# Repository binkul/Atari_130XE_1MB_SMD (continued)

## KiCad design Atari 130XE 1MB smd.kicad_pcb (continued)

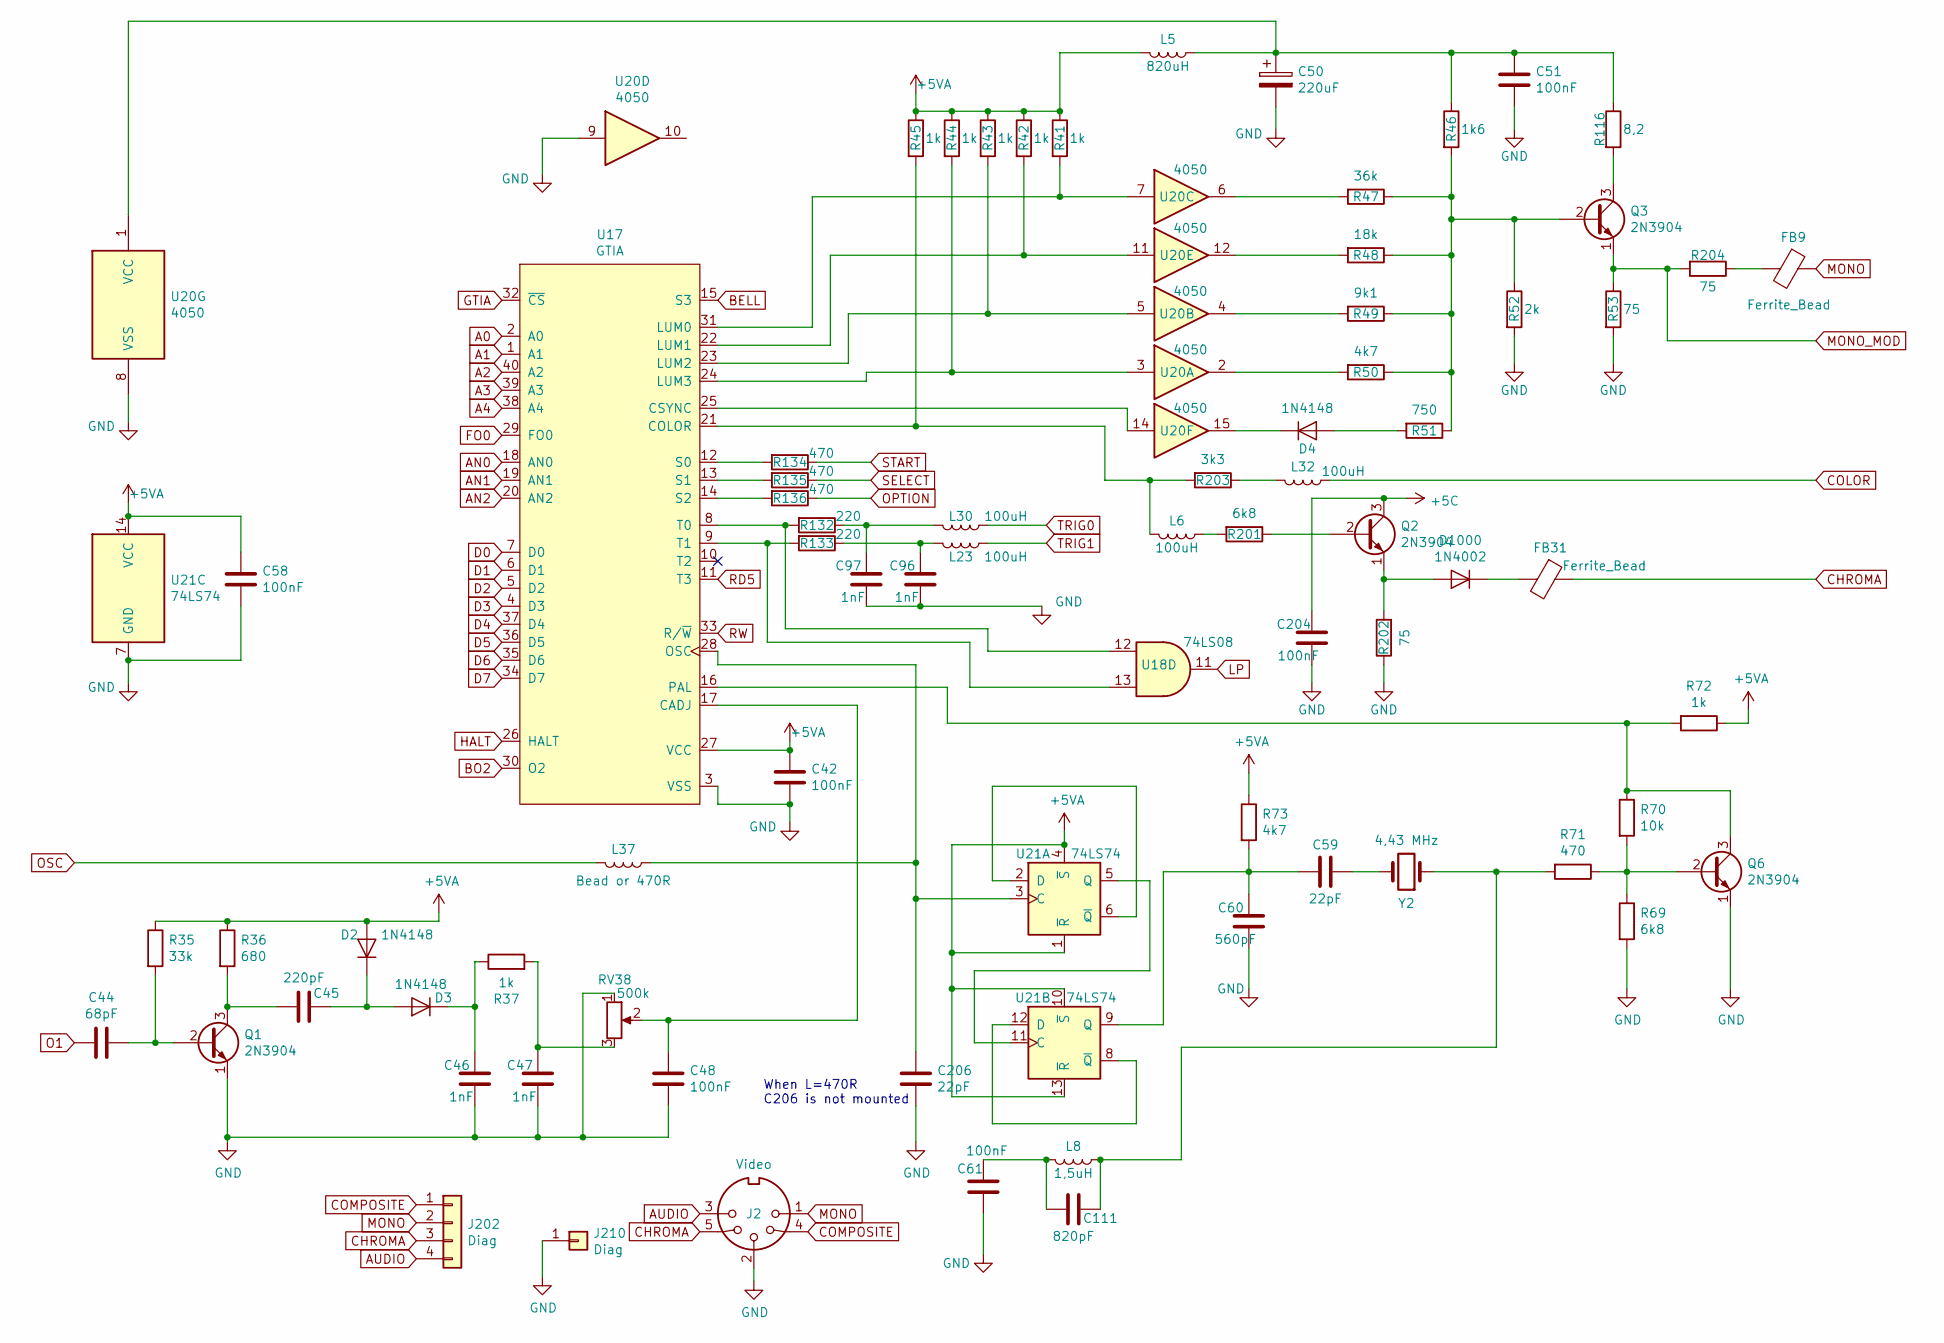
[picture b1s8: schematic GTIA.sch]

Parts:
C42, C48, C51, C58, C61, C204: 100nF; C_1206_3216Metric_Pad1.42x1.75mm_HandSolder
C44: 68pF; C_1206_3216Metric_Pad1.42x1.75mm_HandSolder
C45: 220pF; C_1206_3216Metric_Pad1.42x1.75mm_HandSolder
C46, C47, C96, C97: 1nF; C_1206_3216Metric_Pad1.42x1.75mm_HandSolder
C50: 220uF; CP_Radial_D5.0mm_P2.00mm
C59, C206: 22pF; C_1206_3216Metric_Pad1.42x1.75mm_HandSolder
C60: 560pF; C_1206_3216Metric_Pad1.42x1.75mm_HandSolder
C111: 820pF; C_1206_3216Metric_Pad1.42x1.75mm_HandSolder
D2, D3, D4: 1N4148; D_MiniMELF
D1000: 1N4002; D_MELF_Handsoldering
FB9, FB31: Ferrite_Bead; L_1812_4532Metric_Pad1.30x3.40mm_HandSolder
J2: Video; DIN_5_pin
J202: Diag; PinHeader_1x04_P2.54mm_Vertical
J210: Diag; PinHeader_1x01_P2.54mm_Vertical
L5: 820uH; L_1812_4532Metric_Pad1.30x3.40mm_HandSolder
L6, L23, L30, L32: 100uH; L_1812_4532Metric_Pad1.30x3.40mm_HandSolder
L8: 1,5uH; L_1812_4532Metric_Pad1.30x3.40mm_HandSolder
L37: Bead or 470R; C_1206_3216Metric_Pad1.42x1.75mm_HandSolder
Q1, Q2, Q3: 2N3904; TO-92L_Wide
Q6: 2N3904; TO-92
R35: 33k; R_1206_3216Metric_Pad1.42x1.75mm_HandSolder
R36: 680; R_1206_3216Metric_Pad1.42x1.75mm_HandSolder
R37, R41, R42, R43, R44, R45, R72: 1k; R_1206_3216Metric_Pad1.42x1.75mm_HandSolder
R46: 1k6; R_1206_3216Metric_Pad1.42x1.75mm_HandSolder
R47: 36k; R_1206_3216Metric_Pad1.42x1.75mm_HandSolder
R48: 18k; R_1206_3216Metric_Pad1.42x1.75mm_HandSolder
R49: 9k1; R_1206_3216Metric_Pad1.42x1.75mm_HandSolder
R50, R73: 4k7; R_1206_3216Metric_Pad1.42x1.75mm_HandSolder
R51: 750; R_1206_3216Metric_Pad1.42x1.75mm_HandSolder
R52: 2k; R_1206_3216Metric_Pad1.42x1.75mm_HandSolder
R53, R202, R204: 75; R_1206_3216Metric_Pad1.42x1.75mm_HandSolder
R69, R201: 6k8; R_1206_3216Metric_Pad1.42x1.75mm_HandSolder
R70: 10k; R_1206_3216Metric_Pad1.42x1.75mm_HandSolder
R71, R134, R135, R136: 470; R_1206_3216Metric_Pad1.42x1.75mm_HandSolder
R116: 8,2; R_1206_3216Metric_Pad1.42x1.75mm_HandSolder
R132, R133: 220; R_1206_3216Metric_Pad1.42x1.75mm_HandSolder
R203: 3k3; R_1206_3216Metric_Pad1.42x1.75mm_HandSolder
RV38: 500k; Potentiometer_ACP_CA9-V10_Vertical_Hole
U17: GTIA; DIP-40_W15.24mm_Socket
U18: 74LS08; DIP-14_W7.62mm_Socket
U20: 4050; DIP-16_W7.62mm_Socket
U21: 74LS74; DIP-14_W7.62mm_Socket
Y2: 4,43 MHz; Crystal_HC18-U_Horizontal

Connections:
+5C: C204.2, Q2.3 (C); also elsewhere on the board
+5VA: C42.1, C58.1, D2.2 (A), L5.2, R35.1, R36.1, R41.1, R42.1, R43.1, R44.1, R45.1, R72.1, R73.1, U17.27 (VCC), U21.1 (~R), U21.4 (~S), U21.10 (~S), U21.13 (~R), U21.14 (VCC); also elsewhere on the board
A0: U17.2 (A0); also elsewhere on the board
A1: U17.1 (A1); also elsewhere on the board
A2: U17.40 (A2); also elsewhere on the board
A3: U17.39 (A3); also elsewhere on the board
A4: U17.38 (A4); also elsewhere on the board
AN0: U17.18 (AN0); also elsewhere on the board
AN1: U17.19 (AN1); also elsewhere on the board
AN2: U17.20 (AN2); also elsewhere on the board
AUDIO: J2.3, J202.4; also elsewhere on the board
BELL: U17.15 (S3); also elsewhere on the board
BO2: U17.30 (O2); also elsewhere on the board
CHROMA: FB31.1, J2.5, J202.3
COLOR: L32.1; also elsewhere on the board
COMPOSITE: J2.4, J202.1; also elsewhere on the board
D0: U17.7 (D0); also elsewhere on the board
D1: U17.6 (D1); also elsewhere on the board
D2: U17.5 (D2); also elsewhere on the board
D3: U17.4 (D3); also elsewhere on the board
D4: U17.37 (D4); also elsewhere on the board
D5: U17.36 (D5); also elsewhere on the board
D6: U17.35 (D6); also elsewhere on the board
D7: U17.34 (D7); also elsewhere on the board
FO0: U17.29 (FO0); also elsewhere on the board
GND: C42.2, C46.1, C47.1, C48.1, C50.2, C51.2, C58.2, C60.1, C61.1, C96.1, C97.1, C204.1, C206.1, J2.2, J210.1, Q1.1 (E), Q6.1 (E), R52.2, R53.2, R69.2, R202.1, RV38.1, U17.3 (VSS), U20.8 (VSS), U20.9, U21.7 (GND); also elsewhere on the board
GTIA: U17.32 (~CS); also elsewhere on the board
HALT: U17.26 (HALT); also elsewhere on the board
LP: U18.11; also elsewhere on the board
MONO: FB9.1, J2.1, J202.2
MONO_MOD: Q3.1 (E), R53.1, R204.2; also elsewhere on the board
unnamed: C44.1, Q1.2 (B), R35.2
unnamed: C45.1, D2.1 (K), D3.2 (A)
unnamed: C45.2, Q1.3 (C), R36.2
unnamed: C46.2, D3.1 (K), R37.1
unnamed: C47.2, R37.2, RV38.3
unnamed: C48.2, RV38.2, U17.17 (CADJ)
unnamed: C50.1, C51.1, L5.1, R46.1, R116.1, U20.1 (VCC)
unnamed: C59.1, C60.2, R73.2, U21.9 (Q)
unnamed: C59.2, Y2.2
unnamed: C96.2, L23.2, R133.1
unnamed: C97.2, L30.2, R132.1
unnamed: C111.1, L8.1, R71.2, Y2.1
unnamed: C61.2, C111.2, L8.2
unnamed: C206.2, L37.1, U17.28 (OSC), U21.3 (C)
unnamed: D4.1 (K), U20.15
unnamed: D4.2 (A), R51.2
unnamed: D1000.1 (K), FB31.2
unnamed: D1000.2 (A), Q2.1 (E), R202.2
unnamed: FB9.2, R204.1
unnamed: L6.1, R201.2
unnamed: L6.2, R45.2, R203.2, U17.21 (COLOR)
unnamed: L32.2, R203.1
unnamed: Q2.2 (B), R201.1
unnamed: Q3.2 (B), R46.2, R47.1, R48.1, R49.1, R50.1, R51.1, R52.1
unnamed: Q3.3 (C), R116.2
unnamed: Q6.2 (B), R69.1, R70.2, R71.1
unnamed: Q6.3 (C), R70.1, R72.2, U17.16 (PAL)
unnamed: R41.2, U17.31 (LUM0), U20.7
unnamed: R42.2, U17.22 (LUM1), U20.11
unnamed: R43.2, U17.23 (LUM2), U20.5
unnamed: R44.2, U17.24 (LUM3), U20.3
unnamed: R47.2, U20.6
unnamed: R48.2, U20.12
unnamed: R49.2, U20.4
unnamed: R50.2, U20.2
unnamed: R132.2, U17.8 (T0), U18.12
unnamed: R133.2, U17.9 (T1), U18.13
unnamed: R134.2, U17.12 (S0)
unnamed: R135.2, U17.13 (S1)
unnamed: R136.2, U17.14 (S2)
unnamed: U17.25 (CSYNC), U20.14
unnamed: U21.2 (D), U21.6 (~Q)
unnamed: U21.5 (Q), U21.11 (C)
unnamed: U21.8 (~Q), U21.12 (D)
O1: C44.2; also elsewhere on the board
OPTION: R136.1; also elsewhere on the board
OSC: L37.2; also elsewhere on the board
RD5: U17.11 (T3); also elsewhere on the board
RW: U17.33 (R/~W); also elsewhere on the board
SELECT: R135.1; also elsewhere on the board
START: R134.1; also elsewhere on the board
TRIG0: L30.1; also elsewhere on the board
TRIG1: L23.1; also elsewhere on the board

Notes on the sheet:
When L=470R C206 is not mounted

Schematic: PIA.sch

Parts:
C68: 100nF; C_1206_3216Metric_Pad1.42x1.75mm_HandSolder
C79: 22uF; CP_Radial_D7.5mm_P2.50mm
C80: 1nF; R_1206_3216Metric_Pad1.42x1.75mm_HandSolder
C81, C82, C83, C84, C85, C86, C87, C88, C89, C90, C91, C92: 1nF; C_1206_3216Metric_Pad1.42x1.75mm_HandSolder
FB10, FB11: Ferrite_Bead; L_1812_4532Metric_Pad1.30x3.40mm_HandSolder
L19, L20, L21, L22, L26, L27, L28, L29: 10uH; L_1812_4532Metric_Pad1.30x3.40mm_HandSolder
Q4: 2N3906; TO-92_Wide
R23, R24, R25, R85, R86, R87, R88, R501: 3k; R_1206_3216Metric_Pad1.42x1.75mm_HandSolder
R91: 2k7; R_1206_3216Metric_Pad1.42x1.75mm_HandSolder
R92, R93, R94: 4k7; R_1206_3216Metric_Pad1.42x1.75mm_HandSolder
R117, R119: 100; R_1206_3216Metric_Pad1.42x1.75mm_HandSolder
R118, R120, R121, R122, R123, R124, R125, R126, R127: 220; R_1206_3216Metric_Pad1.42x1.75mm_HandSolder
R206: 3k3; R_1206_3216Metric_Pad1.42x1.75mm_HandSolder
U23: PIA; DIP-40_W15.24mm_Socket

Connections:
+5VA: C68.1, FB10.2, Q4.1 (E), R23.1, R24.1, R25.1, R85.1, R86.1, R87.1, R88.1, R92.1, R93.2, R94.2, R206.1, R501.1, U23.20 (VCC); also elsewhere on the board
A0: U23.35 (A0); also elsewhere on the board
A1: U23.36 (A1); also elsewhere on the board
BACK0: L28.1; also elsewhere on the board
BACK1: L21.1; also elsewhere on the board
BO2: U23.25 (O2); also elsewhere on the board
COMMAND: C84.1, R119.1; also elsewhere on the board
D0: U23.33 (D0); also elsewhere on the board
D1: U23.32 (D1); also elsewhere on the board
D2: U23.31 (D2); also elsewhere on the board
D3: U23.30 (D3); also elsewhere on the board
D4: U23.29 (D4); also elsewhere on the board
D5: U23.28 (D5); also elsewhere on the board
D6: U23.27 (D6); also elsewhere on the board
D7: U23.26 (D7); also elsewhere on the board
FWD0: L29.1; also elsewhere on the board
FWD1: L22.1; also elsewhere on the board
GND: C68.2, C79.2, C80.2, C81.2, C82.2, C83.2, C84.2, C85.2, C86.2, C87.2, C88.2, C89.2, C90.2, C91.2, C92.2, U23.1 (VSS); also elsewhere on the board
INTRUPT: C83.1, R93.1, R118.1; also elsewhere on the board
IRQ: U23.37 (~IRQB), U23.38 (~IRQA); also elsewhere on the board
LEFT0: L27.1; also elsewhere on the board
LEFT1: L20.1; also elsewhere on the board
MTR_CLR: C81.1, FB11.1; also elsewhere on the board
unnamed: C85.1, L29.2, R120.1
unnamed: C86.1, L28.2, R121.1
unnamed: C87.1, L27.2, R122.1
unnamed: C88.1, L26.2, R123.1
unnamed: C89.1, L22.2, R124.1
unnamed: C90.1, L21.2, R125.1
unnamed: C91.1, L20.2, R126.1
unnamed: C92.1, L19.2, R127.1
unnamed: FB11.2, Q4.3 (C)
unnamed: Q4.2 (B), R91.1
unnamed: R86.2, U23.22 (CS0), U23.24 (CS1)
unnamed: R91.2, U23.39 (CA2)
unnamed: R92.2, R117.2, U23.40 (CA1)
unnamed: R118.2, U23.18 (CB1)
unnamed: R94.1, R119.2, U23.19 (CB2)
unnamed: R120.2, U23.2 (PA0)
unnamed: R121.2, U23.3 (PA1)
unnamed: R122.2, U23.4 (PA2)
unnamed: R123.2, U23.5 (PA3)
unnamed: R124.2, U23.6 (PA4)
unnamed: R125.2, U23.7 (PA5)
unnamed: R126.2, U23.8 (PA6)
unnamed: R127.2, U23.9 (PA7)
PB0: R88.2, U23.10 (PB0); also elsewhere on the board
PB1: R85.2, U23.11 (PB1); also elsewhere on the board
PB2: R23.2, U23.12 (PB2); also elsewhere on the board
PB3: R25.2, U23.13 (PB3); also elsewhere on the board
PB4: R24.2, U23.14 (PB4); also elsewhere on the board
PB5: R206.2, U23.15 (PB5); also elsewhere on the board
PB6: R501.2, U23.16 (PB6); also elsewhere on the board
PB7: R87.2, U23.17 (PB7); also elsewhere on the board
PIA: U23.23 (~CS2); also elsewhere on the board
PROCEED: C82.1, R117.1; also elsewhere on the board
READY: C79.1, C80.1, FB10.1; also elsewhere on the board
RIGHT0: L26.1; also elsewhere on the board
RIGHT1: L19.1; also elsewhere on the board
RST: U23.34 (~RST); also elsewhere on the board
RW: U23.21 (R/~W); also elsewhere on the board

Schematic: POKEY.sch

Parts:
C62, C71, C72, C73, C74, C75, C76, C77, C78: 1nF; C_1206_3216Metric_Pad1.42x1.75mm_HandSolder
C63, C64, C65, C66: 47nF; C_1206_3216Metric_Pad1.42x1.75mm_HandSolder
C69, C70: 100nF; C_1206_3216Metric_Pad1.42x1.75mm_HandSolder
C98: 10uF; CP_Radial_D5.0mm_P2.00mm
D5: 1N4148; D_1206_3216Metric_Pad1.42x1.75mm_HandSolder
J201: Diagnostic; PinHeader_1x04_P2.54mm_Vertical
L15, L16, L17, L18: 10uH; L_1812_4532Metric_Pad1.30x3.40mm_HandSolder
R74: 3k; R_1206_3216Metric_Pad1.42x1.75mm_HandSolder
R76, R77, R78, R79: 1k8; R_1206_3216Metric_Pad1.42x1.75mm_HandSolder
R80: 1k; R_1206_3216Metric_Pad1.42x1.75mm_HandSolder
R81, R82, R83, R84: 4k7; R_1206_3216Metric_Pad1.42x1.75mm_HandSolder
R89, R96: 47k; R_1206_3216Metric_Pad1.42x1.75mm_HandSolder
R90, R128, R129, R130, R131: 100; R_1206_3216Metric_Pad1.42x1.75mm_HandSolder
R137: 270; R_1206_3216Metric_Pad1.42x1.75mm_HandSolder
R138, R139, R140, R141, R142, R143, R144, R145, R146, R147, R148, R149, R150, R151, R152, R153: 220; R_1206_3216Metric_Pad1.42x1.75mm_HandSolder
U22: POKEY; DIP-40_W15.24mm_Socket
U24, U25: CD4051B; DIP-16_W7.62mm_Socket

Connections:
+5P: C62.1, C98.1, U22.17 (VCC); also elsewhere on the board
+5VA: C69.1, C70.1, D5.1 (K), R74.1, R80.2, R81.1, R82.1, R83.1, R84.1, R89.2, R96.2, U24.16 (VDD), U25.16 (VDD); also elsewhere on the board
A0: U22.36 (A0); also elsewhere on the board
A1: U22.35 (A1); also elsewhere on the board
A2: U22.34 (A2); also elsewhere on the board
A3: U22.33 (A3); also elsewhere on the board
BO2: U22.7 (O2); also elsewhere on the board
BSC: R137.1; also elsewhere on the board
CLK_IN: C76.1, J201.1, R129.1; also elsewhere on the board
CLK_OUT: C75.1, J201.2, R128.1; also elsewhere on the board
D0: U22.38 (D0); also elsewhere on the board
D1: U22.39 (D1); also elsewhere on the board
D2: U22.40 (D2); also elsewhere on the board
D3: U22.2 (D3); also elsewhere on the board
D4: U22.3 (D4); also elsewhere on the board
D5: U22.4 (D5); also elsewhere on the board
D6: U22.5 (D6); also elsewhere on the board
D7: U22.6 (D7); also elsewhere on the board
DATA_IN: C77.1, J201.3, R130.1; also elsewhere on the board
DATA_OUT: C78.1, J201.4, R131.1; also elsewhere on the board
GND: C62.2, C63.2, C64.2, C65.2, C66.2, C69.2, C70.2, C71.2, C72.2, C73.2, C74.2, C75.2, C76.2, C77.2, C78.2, C98.2, R90.2, U22.1 (VSS), U22.8 (P6), U22.9 (P7), U22.10 (P4), U22.11 (P5), U24.6 (INH), U24.7 (VEE), U24.8 (VSS), U25.6 (INH), U25.7 (VEE), U25.8 (VSS); also elsewhere on the board
IN0: R146.1; also elsewhere on the board
IN1: R147.1; also elsewhere on the board
IN2: R148.1; also elsewhere on the board
IN3: R149.1; also elsewhere on the board
IN4: R150.1; also elsewhere on the board
IN5: R151.1; also elsewhere on the board
IN6: R152.1; also elsewhere on the board
IN7: R153.1; also elsewhere on the board
IRQ: U22.29 (~IRQ); also elsewhere on the board
K0: U22.23 (~K0), U24.11 (A)
K1: U22.22 (~K1), U24.10 (B)
K2: U22.21 (~K2), U24.9 (C)
K3: U22.20 (~K3), U25.11 (A)
K4: U22.19 (~K4), U25.10 (B)
K5: U22.18 (~K5), U25.9 (C)
unnamed: C63.1, R78.2, U22.13 (P3)
unnamed: C64.1, R76.2, U22.15 (P1)
unnamed: C65.1, R77.2, U22.14 (P0)
unnamed: C66.1, R79.2, U22.12 (P2)
unnamed: C71.1, L17.2, R76.1
unnamed: C72.1, L18.2, R77.1
unnamed: C73.1, L15.2, R78.1
unnamed: C74.1, L16.2, R79.1
unnamed: D5.2 (A), R96.1, R137.2, U22.16 (~KR2)
unnamed: R74.2, U22.31 (CS1)
unnamed: R89.1, U22.25 (~KR1), U24.3 (X)
unnamed: R90.1, U25.3 (X)
unnamed: R81.2, R128.2, U22.27 (ACLK)
unnamed: R82.2, R129.2, U22.26 (BCLK)
unnamed: R83.2, R130.2, U22.24 (SID)
unnamed: R84.2, R131.2, U22.28 (SOD)
unnamed: R138.2, U25.4 (X7)
unnamed: R139.2, U25.2 (X6)
unnamed: R140.2, U25.5 (X5)
unnamed: R141.2, U25.1 (X4)
unnamed: R142.2, U25.12 (X3)
unnamed: R143.2, U25.15 (X2)
unnamed: R144.2, U25.14 (X1)
unnamed: R145.2, U25.13 (X0)
unnamed: R146.2, U24.13 (X0)
unnamed: R147.2, U24.14 (X1)
unnamed: R148.2, U24.15 (X2)
unnamed: R149.2, U24.12 (X3)
unnamed: R150.2, U24.1 (X4)
unnamed: R151.2, U24.5 (X5)
unnamed: R152.2, U24.2 (X6)
unnamed: R153.2, U24.4 (X7)
OUT0: R145.1; also elsewhere on the board
OUT1: R144.1; also elsewhere on the board
OUT2: R143.1; also elsewhere on the board
OUT3: R142.1; also elsewhere on the board
OUT4: R141.1; also elsewhere on the board
OUT5: R140.1; also elsewhere on the board
OUT6: R139.1; also elsewhere on the board
OUT7: R138.1; also elsewhere on the board
POKEY: U22.30 (~CS0); also elsewhere on the board
POT_A0: L18.1; also elsewhere on the board
POT_A1: L16.1; also elsewhere on the board
POT_B0: L17.1; also elsewhere on the board
POT_B1: L15.1; also elsewhere on the board
RW: U22.32 (R/~W); also elsewhere on the board
SOUND: R80.1, U22.37 (AUDIO); also elsewhere on the board

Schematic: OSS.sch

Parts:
C28, C99: 100nF; C_1206_3216Metric_Pad1.42x1.75mm_HandSolder
C203: 1uF; C_1206_3216Metric_Pad1.42x1.75mm_HandSolder
D100, D101: 1N4148; D_1206_3216Metric_Pad1.42x1.75mm_HandSolder
J501: TPP_sel; PinHeader_2x02_P2.54mm_Vertical
R508, R509: 4k7; R_1206_3216Metric_Pad1.42x1.75mm_HandSolder
R510: 10k; R_1206_3216Metric_Pad1.42x1.75mm_HandSolder
U5: 27C010; PLCC-32_THT-Socket
U104: 74LS157; SOIC-16_3.9x9.9mm_P1.27mm
U105: 74HC74; SOIC-14_3.9x8.7mm_P1.27mm

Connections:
+5VA: C28.1, C99.1, D100.1 (K), R508.1, R509.2, R510.2, U5.1 (VPP), U5.31 (~PGM), U5.32 (VCC), U104.16 (VCC), U105.10 (~S), U105.13 (~R), U105.14 (VCC); also elsewhere on the board
A0: U5.12 (A0); also elsewhere on the board
A1: U5.11 (A1); also elsewhere on the board
A2: U5.10 (A2); also elsewhere on the board
A3: U5.9 (A3); also elsewhere on the board
A4: U5.8 (A4); also elsewhere on the board
A5: U5.7 (A5); also elsewhere on the board
A6: U5.6 (A6); also elsewhere on the board
A7: U5.5 (A7); also elsewhere on the board
A8: U5.27 (A8); also elsewhere on the board
A9: U5.26 (A9); also elsewhere on the board
A10: U5.23 (A10); also elsewhere on the board
A11: U5.25 (A11); also elsewhere on the board
A12: U5.4 (A12); also elsewhere on the board
A13: U5.28 (A13); also elsewhere on the board
A16: U104.11 (I0c), U105.5 (Q)
D0: U5.13 (D0); also elsewhere on the board
D1: U5.14 (D1); also elsewhere on the board
D2: U5.15 (D2); also elsewhere on the board
D3: U5.17 (D3); also elsewhere on the board
D4: U5.18 (D4); also elsewhere on the board
D5: U5.19 (D5); also elsewhere on the board
D6: U5.20 (D6); also elsewhere on the board
D6XX: U105.3 (C); also elsewhere on the board
D7: U5.21 (D7); also elsewhere on the board
GND: C28.2, C99.2, C203.2, J501.2, J501.4, U5.16 (GND), U104.3 (I1a), U104.6 (I1b), U104.8 (GND), U104.10 (I1c), U104.13 (I1d), U104.14 (I0d), U104.15 (E), U105.2 (D), U105.7 (GND), U105.11 (C), U105.12 (D); also elsewhere on the board
unnamed: C203.1, D100.2 (A), R508.2, U105.1 (~R)
unnamed: D101.1 (K), J501.3, R509.1, U105.4 (~S)
unnamed: J501.1, R510.1, U104.1 (S)
unnamed: U5.3 (A15), U104.4 (Za)
unnamed: U5.29 (A14), U104.7 (Zb)
unnamed: U5.2 (A16), U104.9 (Zc)
OS: U5.22 (~CE), U5.24 (~OE); also elsewhere on the board
PB2: U104.5 (I0b); also elsewhere on the board
PB3: U104.2 (I0a); also elsewhere on the board
RST: D101.2 (A); also elsewhere on the board

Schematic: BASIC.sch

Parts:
C27, C207, C208, C209, C210: 100nF; C_1206_3216Metric_Pad1.42x1.75mm_HandSolder
C211: 22uF; CP_EIA-3528-21_Kemet-B_Pad1.50x2.35mm_HandSolder
C212: 4u7; CP_EIA-3528-21_Kemet-B_Pad1.50x2.35mm_HandSolder
J500: Basic_sel; PinHeader_2x04_P2.54mm_Vertical
R502: 1k; R_1206_3216Metric_Pad1.42x1.75mm_HandSolder
R503, R504, R505, R506: 10k; R_1206_3216Metric_Pad1.42x1.75mm_HandSolder
R507: 1k2; R_1206_3216Metric_Pad1.42x1.75mm_HandSolder
U4: 27C010; PLCC-32_THT-Socket
U100: 74LS157; SOIC-16_3.9x9.9mm_P1.27mm
U101: 74LS74; SOIC-14_3.9x8.7mm_P1.27mm
U102, U103: 74HC02; SOIC-14_3.9x8.7mm_P1.27mm

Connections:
+5VA: C27.1, C207.1, C208.1, C209.1, C210.1, R503.1, R504.1, R505.1, R506.1, R507.1, U4.1 (VPP), U4.31 (~PGM), U4.32 (VCC), U100.16 (VCC), U101.14 (VCC), U102.14 (VCC), U103.14 (VCC); also elsewhere on the board
A0: U4.12 (A0), U101.2 (D); also elsewhere on the board
A1: U4.11 (A1); also elsewhere on the board
A2: U4.10 (A2); also elsewhere on the board
A3: U4.9 (A3), U101.12 (D); also elsewhere on the board
A4: U4.8 (A4); also elsewhere on the board
A5: U4.7 (A5); also elsewhere on the board
A6: U4.6 (A6); also elsewhere on the board
A7: U4.5 (A7); also elsewhere on the board
A8: U4.27 (A8); also elsewhere on the board
A9: U4.26 (A9); also elsewhere on the board
A10: U4.23 (A10); also elsewhere on the board
A11: U4.25 (A11); also elsewhere on the board
A12: U100.3 (I1a), U102.3, U102.5; also elsewhere on the board
A14_sel: J500.3, R505.2, U4.29 (A14)
A15_sel: J500.5, R504.2, U4.3 (A15)
A16_sel: J500.7, R503.2, U4.2 (A16)
BASIC: U100.10 (I1c); also elsewhere on the board
BO2: U102.8, U102.9; also elsewhere on the board
CCTL: U102.11; also elsewhere on the board
D0: U4.13 (D0); also elsewhere on the board
D1: U4.14 (D1); also elsewhere on the board
D2: U4.15 (D2); also elsewhere on the board
D3: U4.17 (D3); also elsewhere on the board
D4: U4.18 (D4); also elsewhere on the board
D5: U4.19 (D5); also elsewhere on the board
D6: U4.20 (D6); also elsewhere on the board
D7: U4.21 (D7); also elsewhere on the board
GND: C27.2, C207.2, C208.2, C209.2, C210.2, C211.2, C212.2, J500.2, J500.4, J500.6, J500.8, R502.2, U4.16 (GND), U100.6 (I1b), U100.8 (GND), U100.15 (E), U101.7 (GND), U102.7 (GND), U103.7 (GND); also elsewhere on the board
unnamed: C211.1, C212.1, R507.2, U101.1 (~R), U101.13 (~R)
unnamed: J500.1, R506.2, U100.1 (S)
unnamed: R502.1, U100.13 (I1d)
unnamed: U100.2 (I0a), U102.1
unnamed: U4.4 (A12), U100.4 (Za)
unnamed: U100.5 (I0b), U102.4
unnamed: U4.28 (A13), U100.7 (Zb)
unnamed: U4.22 (~CE), U4.24 (~OE), U100.9 (Zc)
unnamed: U100.11 (I0c), U103.10
unnamed: U100.14 (I0d), U103.1
unnamed: U101.5 (Q), U103.5
unnamed: U101.6 (~Q), U102.6
unnamed: U101.8 (~Q), U103.6
unnamed: U101.9 (Q), U102.2
unnamed: U101.4 (~S), U101.10 (~S)
unnamed: U101.3 (C), U101.11 (C), U102.13
unnamed: U102.10, U102.12
unnamed: U103.2, U103.3, U103.4, U103.12
unnamed: U103.8, U103.9, U103.13
RD5: U100.12 (Zd); also elsewhere on the board
S5: U103.11; also elsewhere on the board

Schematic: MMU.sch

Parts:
C26: 100nF; C_1206_3216Metric_Pad1.42x1.75mm_HandSolder
R12: 3k; R_Axial_DIN0207_L3.6mm_D2.2mm_P10.16mm_Horizontal
R13, R14: 1k; R_1206_3216Metric_Pad1.42x1.75mm_HandSolder
R15: 3k; R_1206_3216Metric_Pad1.42x1.75mm_HandSolder
U2: 74LS138; DIP-16_W7.62mm_Socket
U3: MMU; DIP-20_W7.62mm_Socket
U18: 74LS08; DIP-14_W7.62mm_Socket

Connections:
+5VA: C26.1, R12.1, R15.1, U2.16 (VCC), U3.20 (VCC); also elsewhere on the board
A8: U2.1 (A0); also elsewhere on the board
A9: U2.2 (A1); also elsewhere on the board
A10: U2.3 (A2); also elsewhere on the board
A11: U3.1 (A11); also elsewhere on the board
A12: U3.2 (A12); also elsewhere on the board
A13: U3.3 (A13); also elsewhere on the board
A14: U3.4 (A14); also elsewhere on the board
A15: U3.5 (A15); also elsewhere on the board
BASIC: U3.13 (~BASIC); also elsewhere on the board
BE: U3.18 (~BE); also elsewhere on the board
CASINH: U3.16 (~CI); also elsewhere on the board
CCTL: U2.10 (O5); also elsewhere on the board
D1XX: U2.14 (O1); also elsewhere on the board
D6XX: U2.9 (O6); also elsewhere on the board
E3: R12.2, U2.6 (E3)
GND: C26.2, R13.2, R14.2, U2.5 (E2), U2.8 (GND), U3.10 (VSS); also elsewhere on the board
GTIA: U18.8; also elsewhere on the board
MAP: U3.6 (~MAP); also elsewhere on the board
MPD: R15.2, U3.14 (~MPD); also elsewhere on the board
unnamed: U2.4 (E1), U3.17 (~IO)
unnamed: U2.15 (O0), U18.9, U18.10
OS: U3.15 (~OS); also elsewhere on the board
PB0: U3.9 (REN); also elsewhere on the board
PIA: U2.12 (O3); also elsewhere on the board
POKEY: U2.13 (O2); also elsewhere on the board
RD4: R14.1, U3.7 (RD4); also elsewhere on the board
RD5: R13.1, U3.8 (RD5); also elsewhere on the board
REF: U3.11 (~REF); also elsewhere on the board
S4: U3.19 (~S4); also elsewhere on the board
S5: U3.12 (~S5); also elsewhere on the board

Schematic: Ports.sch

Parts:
C93: 100nF; C_1206_3216Metric_Pad1.42x1.75mm_HandSolder
C94, C95: 10nF; C_1206_3216Metric_Pad1.42x1.75mm_HandSolder
C102: 1nF; C_1206_3216Metric_Pad1.42x1.75mm_HandSolder
FB12, FB102: Ferrite_Bead; L_1812_4532Metric_Pad1.30x3.40mm_HandSolder
J1: SIO; SIO_Slot
J5, J6: Joystick_Port; Joystick_Pport
J8: Keyboard; PinHeader_1x24_P2.54mm_Vertical
L25: 10uH; L_1812_4532Metric_Pad1.30x3.40mm_HandSolder
R95: 1k; R_1206_3216Metric_Pad1.42x1.75mm_HandSolder

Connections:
+5P: FB12.1, L25.2; also elsewhere on the board
+5VA: C93.1, C94.1, FB12.2, J8.1, R95.2; also elsewhere on the board
BACK0: J6.2 (Back); also elsewhere on the board
BACK1: J5.2 (Back); also elsewhere on the board
BSC: J8.20; also elsewhere on the board
CLK_IN: J1.1 (CLK_IN); also elsewhere on the board
CLK_OUT: J1.2 (CLK_OUT); also elsewhere on the board
COMMAND: J1.7 (Command); also elsewhere on the board
DATA_IN: J1.3 (Data_In); also elsewhere on the board
DATA_OUT: J1.5 (Data_Out); also elsewhere on the board
FWD0: J6.1 (FWD); also elsewhere on the board
FWD1: J5.1 (FWD); also elsewhere on the board
GND: C93.2, C94.2, C95.2, C102.2, J1.4 (GND), J1.6 (GND), J5.8 (GND), J6.8 (GND), J8.3; also elsewhere on the board
IN0: J8.17; also elsewhere on the board
IN1: J8.11; also elsewhere on the board
IN2: J8.8; also elsewhere on the board
IN3: J8.16; also elsewhere on the board
IN4: J8.19; also elsewhere on the board
IN5: J8.10; also elsewhere on the board
IN6: J8.4; also elsewhere on the board
IN7: J8.9; also elsewhere on the board
INTRUPT: J1.13 (Intrupt); also elsewhere on the board
LEFT0: J6.3 (Left); also elsewhere on the board
LEFT1: J5.3 (Left); also elsewhere on the board
MTR_CLR: J1.8 (Mtr_Ctrl); also elsewhere on the board
unnamed: C95.1, J8.2, R95.1
unnamed: C102.1, FB102.1, J5.7 (VCC), J6.7 (VCC)
unnamed: FB102.2, L25.1
OPTION: J8.23; also elsewhere on the board
OUT0: J8.18; also elsewhere on the board
OUT1: J8.13; also elsewhere on the board
OUT2: J8.15; also elsewhere on the board
OUT3: J8.5; also elsewhere on the board
OUT4: J8.14; also elsewhere on the board
OUT5: J8.6; also elsewhere on the board
OUT6: J8.12; also elsewhere on the board
OUT7: J8.7; also elsewhere on the board
POT_A0: J6.9 (Pot_A); also elsewhere on the board
POT_A1: J5.9 (Pot_A); also elsewhere on the board
POT_B0: J6.5 (Pot_B); also elsewhere on the board
POT_B1: J5.5 (Pot_B); also elsewhere on the board
PROCEED: J1.9 (Proceed); also elsewhere on the board
READY: J1.10 (VCC); also elsewhere on the board
RESET: J8.24; also elsewhere on the board
RIGHT0: J6.4 (Right); also elsewhere on the board
RIGHT1: J5.4 (Right); also elsewhere on the board
SELECT: J8.22; also elsewhere on the board
SIOAUDIO: J1.11 (SIO_Audio); also elsewhere on the board
START: J8.21; also elsewhere on the board
TRIG0: J6.6 (Trig); also elsewhere on the board
TRIG1: J5.6 (Trig); also elsewhere on the board

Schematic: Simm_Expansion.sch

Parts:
C120, C121, C122, C124, C125: 100nF; C_1206_3216Metric_Pad1.42x1.75mm_HandSolder
C123: 100uF; CP_Elec_6.3x9.9
J10: Mem_on_off; PinHeader_2x02_P2.54mm_Vertical
J12: Conn_02x04_Odd_Even; PinHeader_2x04_P2.00mm_Vertical
R97, R98: 10k; R_1206_3216Metric_Pad1.42x1.75mm_HandSolder
R110, R111: 33; R_1206_3216Metric_Pad1.42x1.75mm_HandSolder
U40: GAL20V8_DIP; DIP-24_W7.62mm_Socket
U41: 74LS157; SOP-16_4.4x10.4mm_P1.27mm
U42: 74LS175; SOP-16_4.4x10.4mm_P1.27mm
U43, U44: DRAM_1MB_4bit; SOJ-26
U45: 74HC04; SOIC-14_3.9x8.7mm_P1.27mm

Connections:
+5VA: C120.1, C121.1, C122.1, C123.1, C124.1, C125.1, R97.1, R98.1, U40.24 (VCC), U41.16 (VCC), U42.1 (~Mr), U42.16 (VCC), U43.10 (VCC), U44.10 (VCC), U45.14 (VCC); also elsewhere on the board
A14: U40.3 (I2); also elsewhere on the board
A15: U40.4 (I3); also elsewhere on the board
BE: U42.7 (Q1); also elsewhere on the board
CAS: U40.8 (I7); also elsewhere on the board
CASMAN: R110.2; also elsewhere on the board
DQ0: U44.1 (DQ0); also elsewhere on the board
DQ1: U44.2 (DQ1); also elsewhere on the board
DQ2: U44.18 (DQ2); also elsewhere on the board
DQ3: U44.19 (DQ3); also elsewhere on the board
DQ4: U43.1 (DQ0); also elsewhere on the board
DQ5: U43.2 (DQ1); also elsewhere on the board
DQ6: U43.18 (DQ2); also elsewhere on the board
DQ7: U43.19 (DQ3); also elsewhere on the board
FA14: U40.18 (F3); also elsewhere on the board
FA15: U40.19 (F4); also elsewhere on the board
GND: C120.2, C121.2, C122.2, C123.2, C124.2, C125.2, J10.1, J10.3, U40.12 (GND), U40.13 (I11/OE), U41.8 (GND), U41.15 (E), U42.8 (GND), U43.16 (~OE), U43.20 (VSS), U44.16 (~OE), U44.20 (VSS), U45.7 (GND); also elsewhere on the board
HALT: U40.14 (I12); also elsewhere on the board
MAP: U42.2 (Q0); also elsewhere on the board
unnamed: J10.2, R97.2, U40.10 (I9)
unnamed: J10.4, R98.2, U40.9 (I8)
unnamed: J12.4, U45.8
unnamed: J12.6, U45.11, U45.12
unnamed: J12.8, U45.4, U45.5
unnamed: R110.1, U40.17 (F2)
unnamed: R111.1, U43.17 (~CAS), U44.17 (~CAS)
unnamed: R111.2, U40.16 (F1)
unnamed: U40.15 (F0), U42.9 (Cp)
unnamed: U40.22 (F7), U41.2 (I0a)
unnamed: U41.4 (Za), U43.15 (A8), U44.15 (A8)
unnamed: U41.7 (Zb), U43.5 (A9), U44.5 (A9)
unnamed: U45.2, U45.3
unnamed: U45.9, U45.10
unnamed: U45.6, U45.13
O2: U40.21 (F6); also elsewhere on the board
PB1: U41.6 (I1b), U42.5 (D1); also elsewhere on the board
PB2: U40.5 (I4); also elsewhere on the board
PB3: U40.6 (I5); also elsewhere on the board
PB4: U40.7 (I6); also elsewhere on the board
PB5: U40.23 (I13); also elsewhere on the board
PB6: U41.3 (I1a); also elsewhere on the board
PB7: U41.5 (I0b), U42.4 (D0); also elsewhere on the board
RA0: U43.6 (A0), U44.6 (A0); also elsewhere on the board
RA1: U43.7 (A1), U44.7 (A1); also elsewhere on the board
RA2: U43.8 (A2), U44.8 (A2); also elsewhere on the board
RA3: U43.9 (A3), U44.9 (A3); also elsewhere on the board
RA4: U43.11 (A4), U44.11 (A4); also elsewhere on the board
RA5: U43.12 (A5), U44.12 (A5); also elsewhere on the board
RA6: U43.13 (A6), U44.13 (A6); also elsewhere on the board
RA7: U43.14 (A7), U44.14 (A7); also elsewhere on the board
RAS: J12.2, U45.1; also elsewhere on the board
RAS_out: J12.1, J12.3, J12.5, J12.7, U40.1 (I0/Clk), U41.1 (S), U43.4 (~RAS), U44.4 (~RAS); also elsewhere on the board
REF: U40.2 (I1); also elsewhere on the board
WRT: U43.3 (~WE), U44.3 (~WE); also elsewhere on the board

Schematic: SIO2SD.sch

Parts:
C220, C221: 22p; C_1206_3216Metric_Pad1.42x1.75mm_HandSolder
C222, C223, C224: 100n; C_1206_3216Metric_Pad1.42x1.75mm_HandSolder
C225, C226, C227, C228, C229: 22n; C_1206_3216Metric_Pad1.42x1.75mm_HandSolder
C230: 10n; C_1206_3216Metric_Pad1.42x1.75mm_HandSolder
C231: 220uF; CP_EIA-7343-40_Kemet-Y_Pad2.25x2.55mm_HandSolder
D200: 1N4001; D_MELF
J203: Micro_SD_Card; MCC SDMicro
J204: ISP; IDC-Header_2x03_P2.54mm_Vertical
J205: SIO; PinHeader_2x03_P2.00mm_Vertical
J206: SIOLED1; PinHeader_1x02_P2.54mm_Vertical
J207: LCD 2x16; PinHeader_1x08_P2.54mm_Vertical
J208: SD buttons; PinHeader_1x05_P2.54mm_Vertical
J209: SD config; PinHeader_2x03_P2.54mm_Vertical
J211: SIOLED2; PinHeader_1x02_P2.54mm_Vertical
J212: SIOLED3; PinHeader_1x02_P2.54mm_Vertical
J213: SD_conn; PinHeader_1x07_P2.54mm_Vertical
R220: 10k; R_1206_3216Metric_Pad1.42x1.75mm_HandSolder
R221: 4k7; R_1206_3216Metric_Pad1.42x1.75mm_HandSolder
R222, R223, R224: 220; R_1206_3216Metric_Pad1.42x1.75mm_HandSolder
U200: ATmega32-16AU; TQFP-44_10x10mm_P0.8mm
U201: 74HC245; SOIC-20W_7.5x12.8mm_P1.27mm
U202: LM2936-3.3; SOT-223-3_TabPin2
Y200: Crystal; Crystal_HC18-U_Vertical

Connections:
+3V3: C222.1, C230.1, C231.1, J203.4 (VDD), J213.3, U201.1 (A->B), U201.20 (VCC), U202.3 (VO)
+5VA: C223.1, C224.1, J204.2, R220.1, R221.1, R222.1, R223.1, R224.1, U200.5 (VCC), U200.17 (VCC), U200.27 (AVCC), U200.38 (VCC), U202.1 (VI); also elsewhere on the board
COMMAND: J205.6; also elsewhere on the board
DATA_IN: J205.4; also elsewhere on the board
DATA_OUT: J205.2; also elsewhere on the board
GND: C220.2, C221.2, C222.2, C223.2, C224.2, C225.1, C226.1, C227.1, C228.1, C229.1, C230.2, C231.2, J203.6 (VSS), J203.11 (VSS), J203.12 (Shield), J204.6, J209.2, J209.4, J209.6, J213.7, U200.6 (GND), U200.18 (GND), U200.28 (GND), U200.29 (AREF), U200.39 (GND), U201.10 (GND), U201.19 (CE), U202.2 (GND); also elsewhere on the board
unnamed: C220.1, U200.7 (XTAL2), Y200.2
unnamed: C221.1, U200.8 (XTAL1), Y200.1
unnamed: C225.2, J208.5, U200.40 (PB0)
unnamed: C226.2, J208.4, U200.41 (PB1)
unnamed: C227.2, J208.3, U200.42 (PB2)
unnamed: C228.2, J208.2, U200.43 (PB3)
unnamed: C229.2, J208.1, U200.44 (PB4)
unnamed: D200.1 (K), U200.10 (PD1)
unnamed: D200.2 (A), J205.3
unnamed: J203.2 (DAT3/CS), J213.5, U201.16 (B2)
unnamed: J203.3 (CMD/MOSI), J213.4, U201.17 (B1)
unnamed: J203.5 (CLK/SCK), J213.2, U201.18 (B0)
unnamed: J203.7 (DAT0/MISO), J213.1, U200.22 (PC3)
unnamed: J203.9 (COM), J213.6, U200.23 (PC4)
unnamed: J204.1, U200.2 (PB6)
unnamed: J204.3, U200.3 (PB7)
unnamed: J204.4, U200.1 (PB5)
unnamed: J204.5, R220.2, U200.4 (~RESET)
unnamed: J205.1, R221.2, U200.9 (PD0)
unnamed: J205.5, U200.11 (PD2)
unnamed: J206.1, R222.2
unnamed: J206.2, U200.26 (PC7)
unnamed: J207.1, U200.37 (PA0)
unnamed: J207.2, U200.36 (PA1)
unnamed: J207.3, U200.35 (PA2)
unnamed: J207.4, U200.34 (PA3)
unnamed: J207.5, U200.33 (PA4)
unnamed: J207.6, U200.32 (PA5)
unnamed: J207.7, U200.31 (PA6)
unnamed: J207.8, U200.30 (PA7)
unnamed: J209.1, U200.14 (PD5)
unnamed: J209.3, U200.15 (PD6)
unnamed: J209.5, U200.16 (PD7)
unnamed: J211.1, R223.2
unnamed: J211.2, U200.25 (PC6)
unnamed: J212.1, R224.2
unnamed: J212.2, U200.24 (PC5)
unnamed: U200.19 (PC0), U201.4 (A2)
unnamed: U200.20 (PC1), U201.3 (A1)
unnamed: U200.21 (PC2), U201.2 (A0)

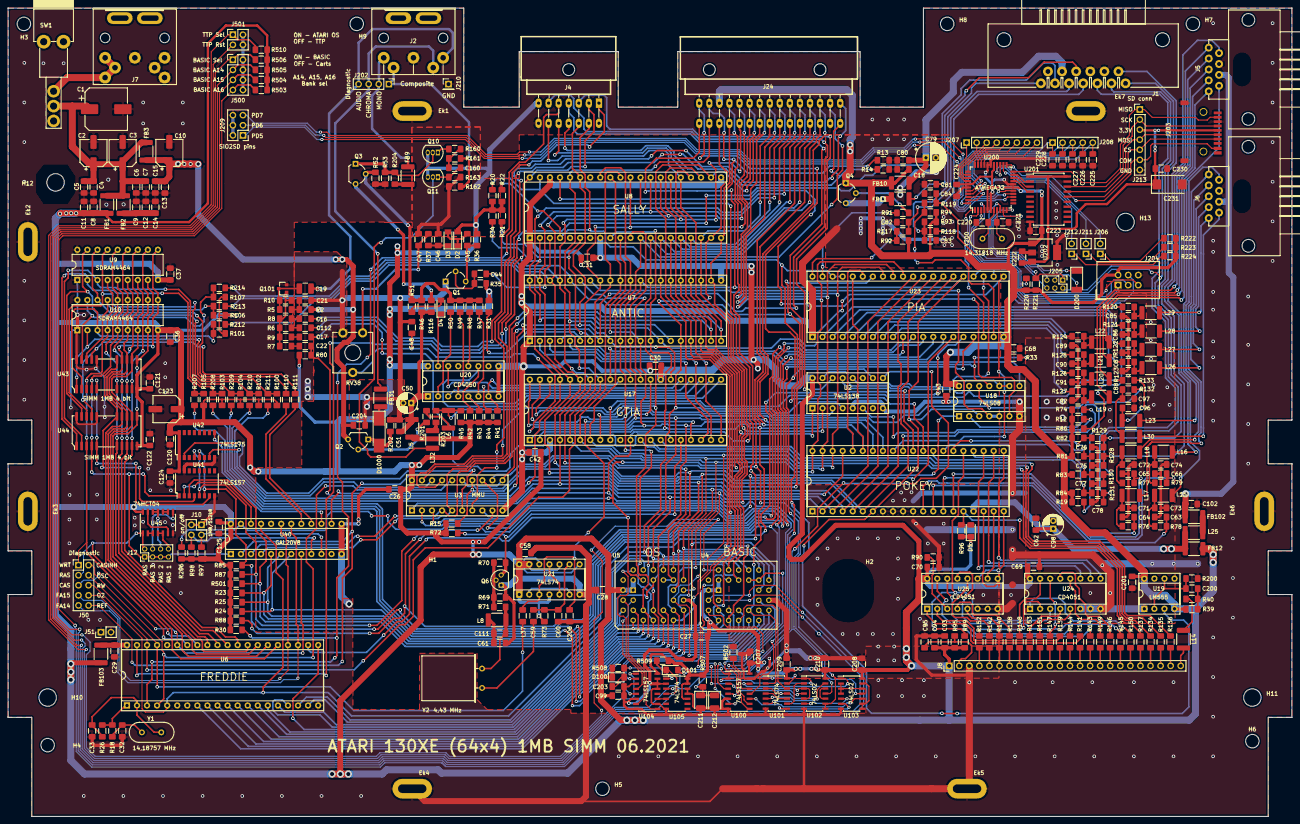
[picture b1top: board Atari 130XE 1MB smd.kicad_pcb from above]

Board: 2 copper layers, 324.0 x 204.0 mm, 397 parts (0 on the bottom side), 366 nets.

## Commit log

2022-03-18 Add all files
2022-03-21 SMD power
2022-03-21 SMD Audio
2022-03-21 SMD ram
2022-03-27 Basic smd
2022-04-09 Basic and os
2022-05-08 PAL to smd
2022-05-08 ROM refactoring
2022-05-22 SMD continue
2022-06-28 Almost finished
2022-07-10 gerber
2022-07-10 add 74ls04
2022-07-10 text on top
2022-07-31 SIO2SD schema
2022-08-19 Final Atmega32
2022-08-21 final inspection
